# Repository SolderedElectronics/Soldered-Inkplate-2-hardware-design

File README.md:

# Inkplate 2 Hardware design

## About the product

|  |
| :----------------------------------------------------------: |
|      [Buy Inkplate 2](https://www.solde.red/333166)      |

The Inkplate 2 is an Arduino-compatible board that features a 2.13" three-color e-paper display. It is a plug-and-play device, programmable via USB port, and controlled by an ESP32 microcontroller. Moreover, it connects to the internet via WiFi or Bluetooth. Since it uses only 8uA in low-power mode, it can last for months on a single Li-ion battery charge. It's simple enough to be used by beginners, but it also offers plenty of features and a user-friendly platform for advanced users. Inkplate 2 has it all, packed on a small-factor board.

If you're like us, when you first saw an e-book reader, you thought "If only I could use a screen like this in my project". Thanks to the exceptional sharpness and contrast, the ability to display in sunlight and truly unprecedented efficiency in terms of energy (it consumes energy only when changing the content on the screen), electronic paper is the ideal choice for many applications. Inkplate 2, continuing the tradition of the now well-known Inkplate series, offers a variation of e-paper accessible to hobbyists and everyone else in a way that we have created a plug-and-play hardware that is really easy to use, and is compatible with Arduino and micropython.

## Repository contents

All Soldered Electronics hardware designed in KiCAD, and repositories are organized in the following way:

- CAD folder - contains KiCAD files (Schematics, Board, Panel Board), sorted by version. Change log lists all changes between versions.
- OUTPUTS - contains useful files, such as Bill of Materials (BOM), PDF of schematics, 3D .step file of the board and gerber files, sorted by version. 
- OUTPUTS -> Compliance - Certificates and useful legal stuff. 

## Want to contribute?

Please feel free to submit a pull request if you have any contributions. We encourage you to submit an issue or pull request if you find a bug. 

## About Soldered

At Soldered, we design and manufacture a wide selection of electronic products to help you turn your ideas into acts and bring you one step closer to your final project. Our products are intented for makers and crafted in-house by our experienced team in Osijek, Croatia. We believe that sharing is a crucial element for improvement and innovation, and we work hard to stay connected with all our makers regardless of their skill or experience level. Therefore, all our products are open-source. Finally, we always have your back. If you face any problem concerning either your shopping experience or your electronics project, our team will help you deal with it, offering efficient customer service and cost-free technical support anytime. Some of those might be useful for you:

- [Web Store](https://www.soldered.com/shop)
- [Tutorials & Projects](https://soldered.com/learn)
- [Community & Technical support](https://soldered.com/community)

## License info

All Soldered open-source hardware (OSH) is under The TAPR Open Hardware License. Read more in the LICENSE file. 

No warranty - all designs in this repository are distributed in the hope that they will be useful, but without any warranty. They are provided "AS IS", therefore without warranty of any kind, either expressed or implied. The entire quality and performance of what you do with the contents of this repository are your responsibility. In no event, Soldered Electronics will be liable for your damages, losses, including any general, special, incidental or consequential damage arising out of the use or inability to use the contents of this repository. 

## Have fun! 
And thank you from your fellow makers at Soldered Electronics.

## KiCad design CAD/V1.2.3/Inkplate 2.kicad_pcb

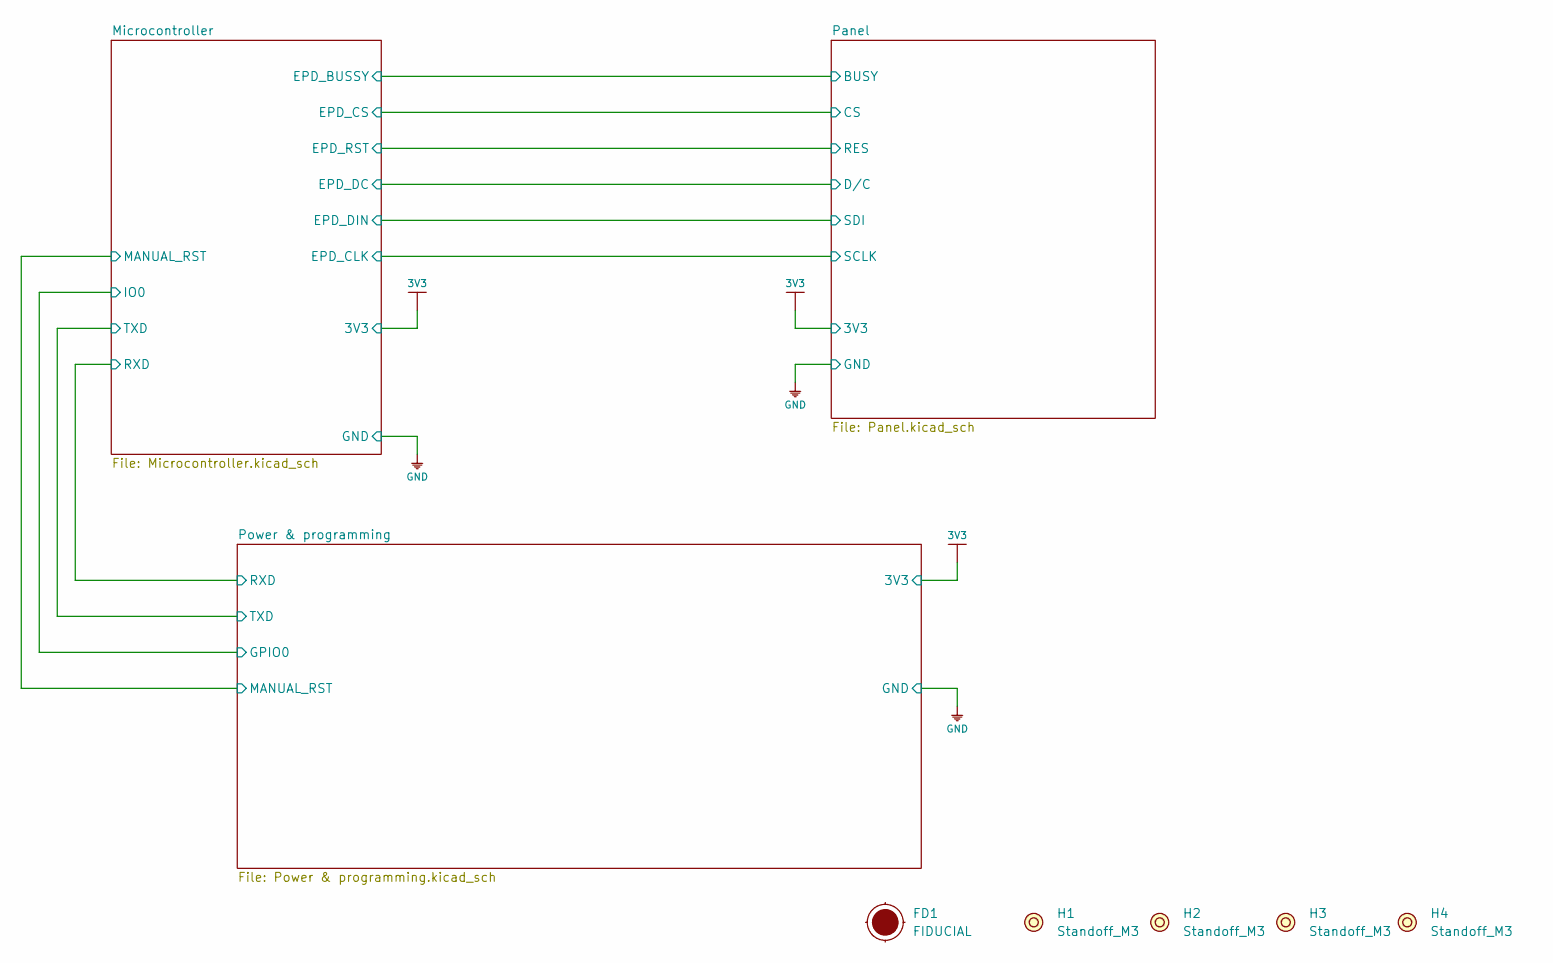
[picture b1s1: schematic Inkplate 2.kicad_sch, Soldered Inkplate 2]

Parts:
FD1: FIDUCIAL; FIDUCIAL_23
H1, H2, H3, H4: Standoff_M3

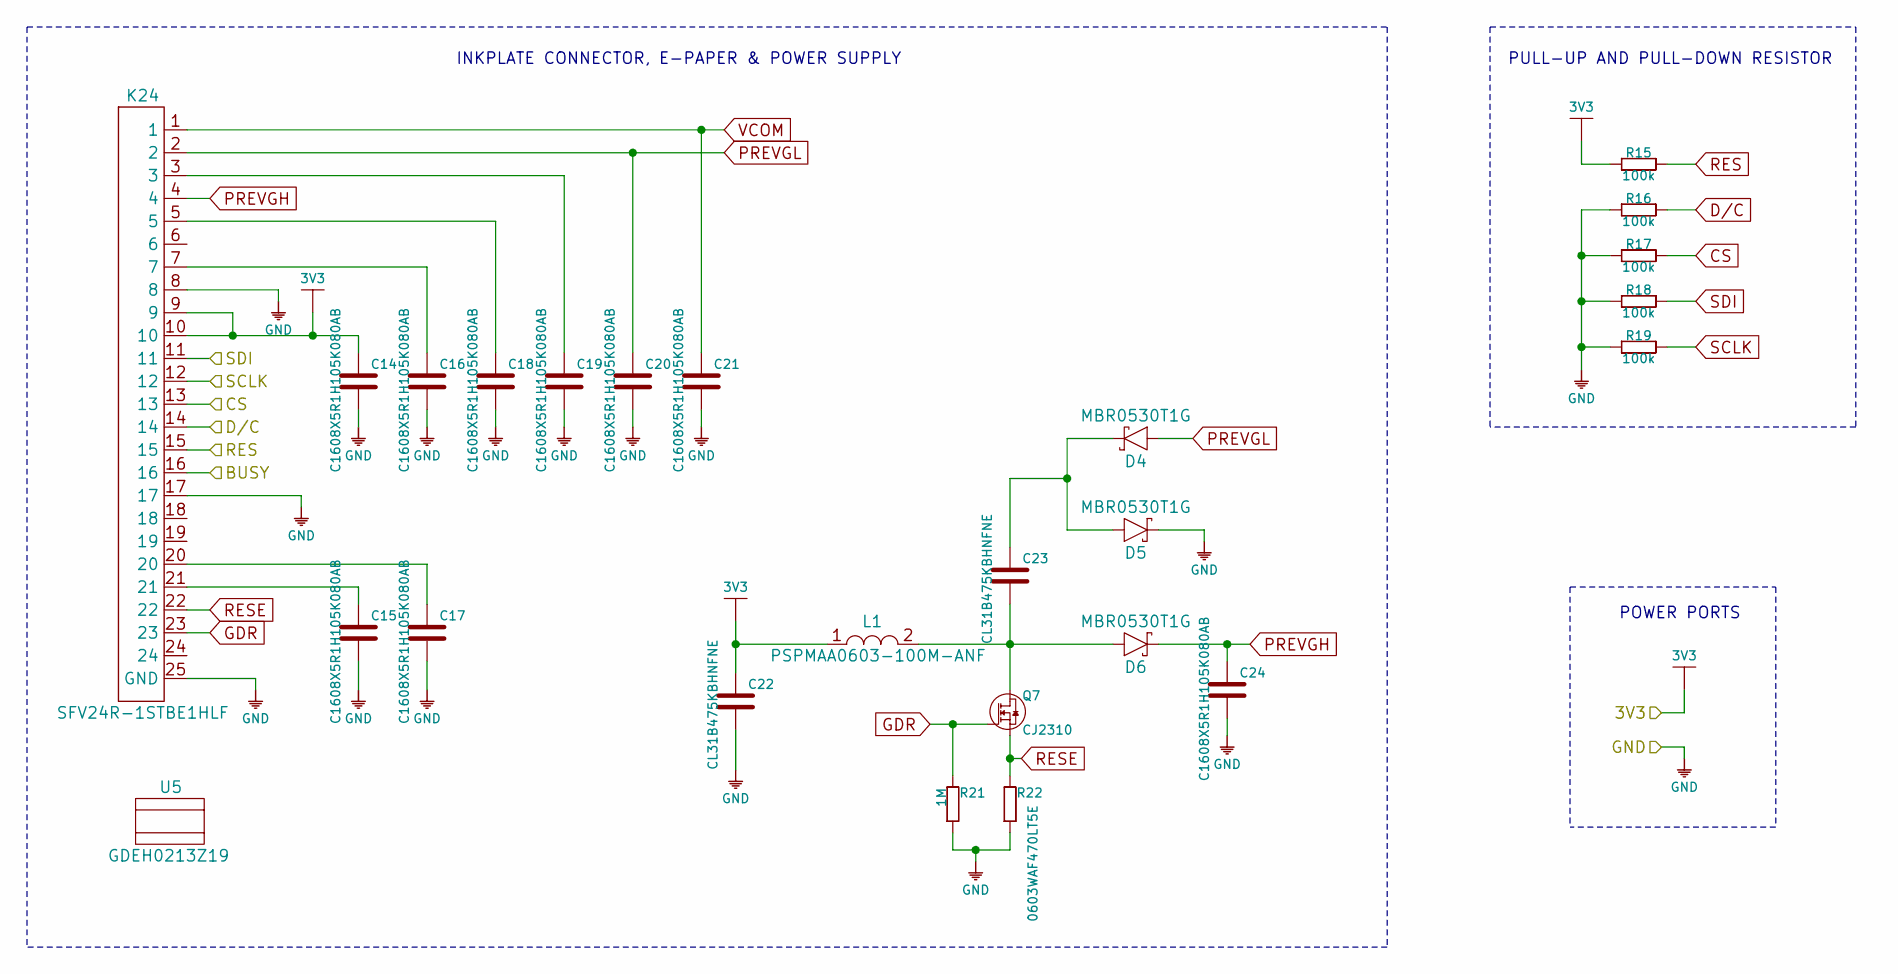
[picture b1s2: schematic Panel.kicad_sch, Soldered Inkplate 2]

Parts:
C14, C15, C16, C17, C18, C19, C20, C21, C24: C1608X5R1H105K080AB; 0603C
C22, C23: CL31B475KBHNFNE; 1206C
D4, D5, D6: MBR0530T1G; SOD-123
K24: SFV24R-1STBE1HLF; SFV24R-2STBE1HLF
L1: PSPMAA0603-100M-ANF; Inductor_SMD_7x6.6
Q7: CJ2310; SOT-23-3
R15, R16, R17, R18, R19: 100k; 0603R
R21: 1M; 0603R
R22: 0603WAF470LT5E; 0603R
U5: GDEH0213Z19

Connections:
3V3: C14.2, C22.2, K24.9, K24.10, L1.1, R15.1; also elsewhere on the board
/Microcontroller/EPD_BUSSY: K24.16; also elsewhere on the board
CS: K24.13, R17.2; also elsewhere on the board
D/C: K24.14, R16.2; also elsewhere on the board
GDR: K24.23, Q7.1 (G), R21.2
GND: C14.1, C15.1, C16.1, C17.1, C18.1, C19.1, C20.1, C21.1, C22.1, C24.1, D5.1 (C), K24.8, K24.17, K24.25 (GND), R16.1, R17.1, R18.1, R19.1, R21.1, R22.1; also elsewhere on the board
unnamed: C15.2, K24.21
unnamed: C16.2, K24.7
unnamed: C17.2, K24.20
unnamed: C18.2, K24.5
unnamed: C19.2, K24.3
unnamed: C23.1, D6.2 (A), L1.2, Q7.3 (D)
unnamed: C23.2, D4.1 (C), D5.2 (A)
PREVGH: C24.2, D6.1 (C), K24.4
PREVGL: C20.2, D4.2 (A), K24.2
RES: K24.15, R15.2; also elsewhere on the board
RESE: K24.22, Q7.2 (S), R22.2
SCLK: K24.12, R19.2; also elsewhere on the board
SDI: K24.11, R18.2; also elsewhere on the board
VCOM: C21.2, K24.1

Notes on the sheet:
INKPLATE CONNECTOR, E-PAPER & POWER SUPPLY
POWER PORTS
PULL-UP AND PULL-DOWN RESISTOR

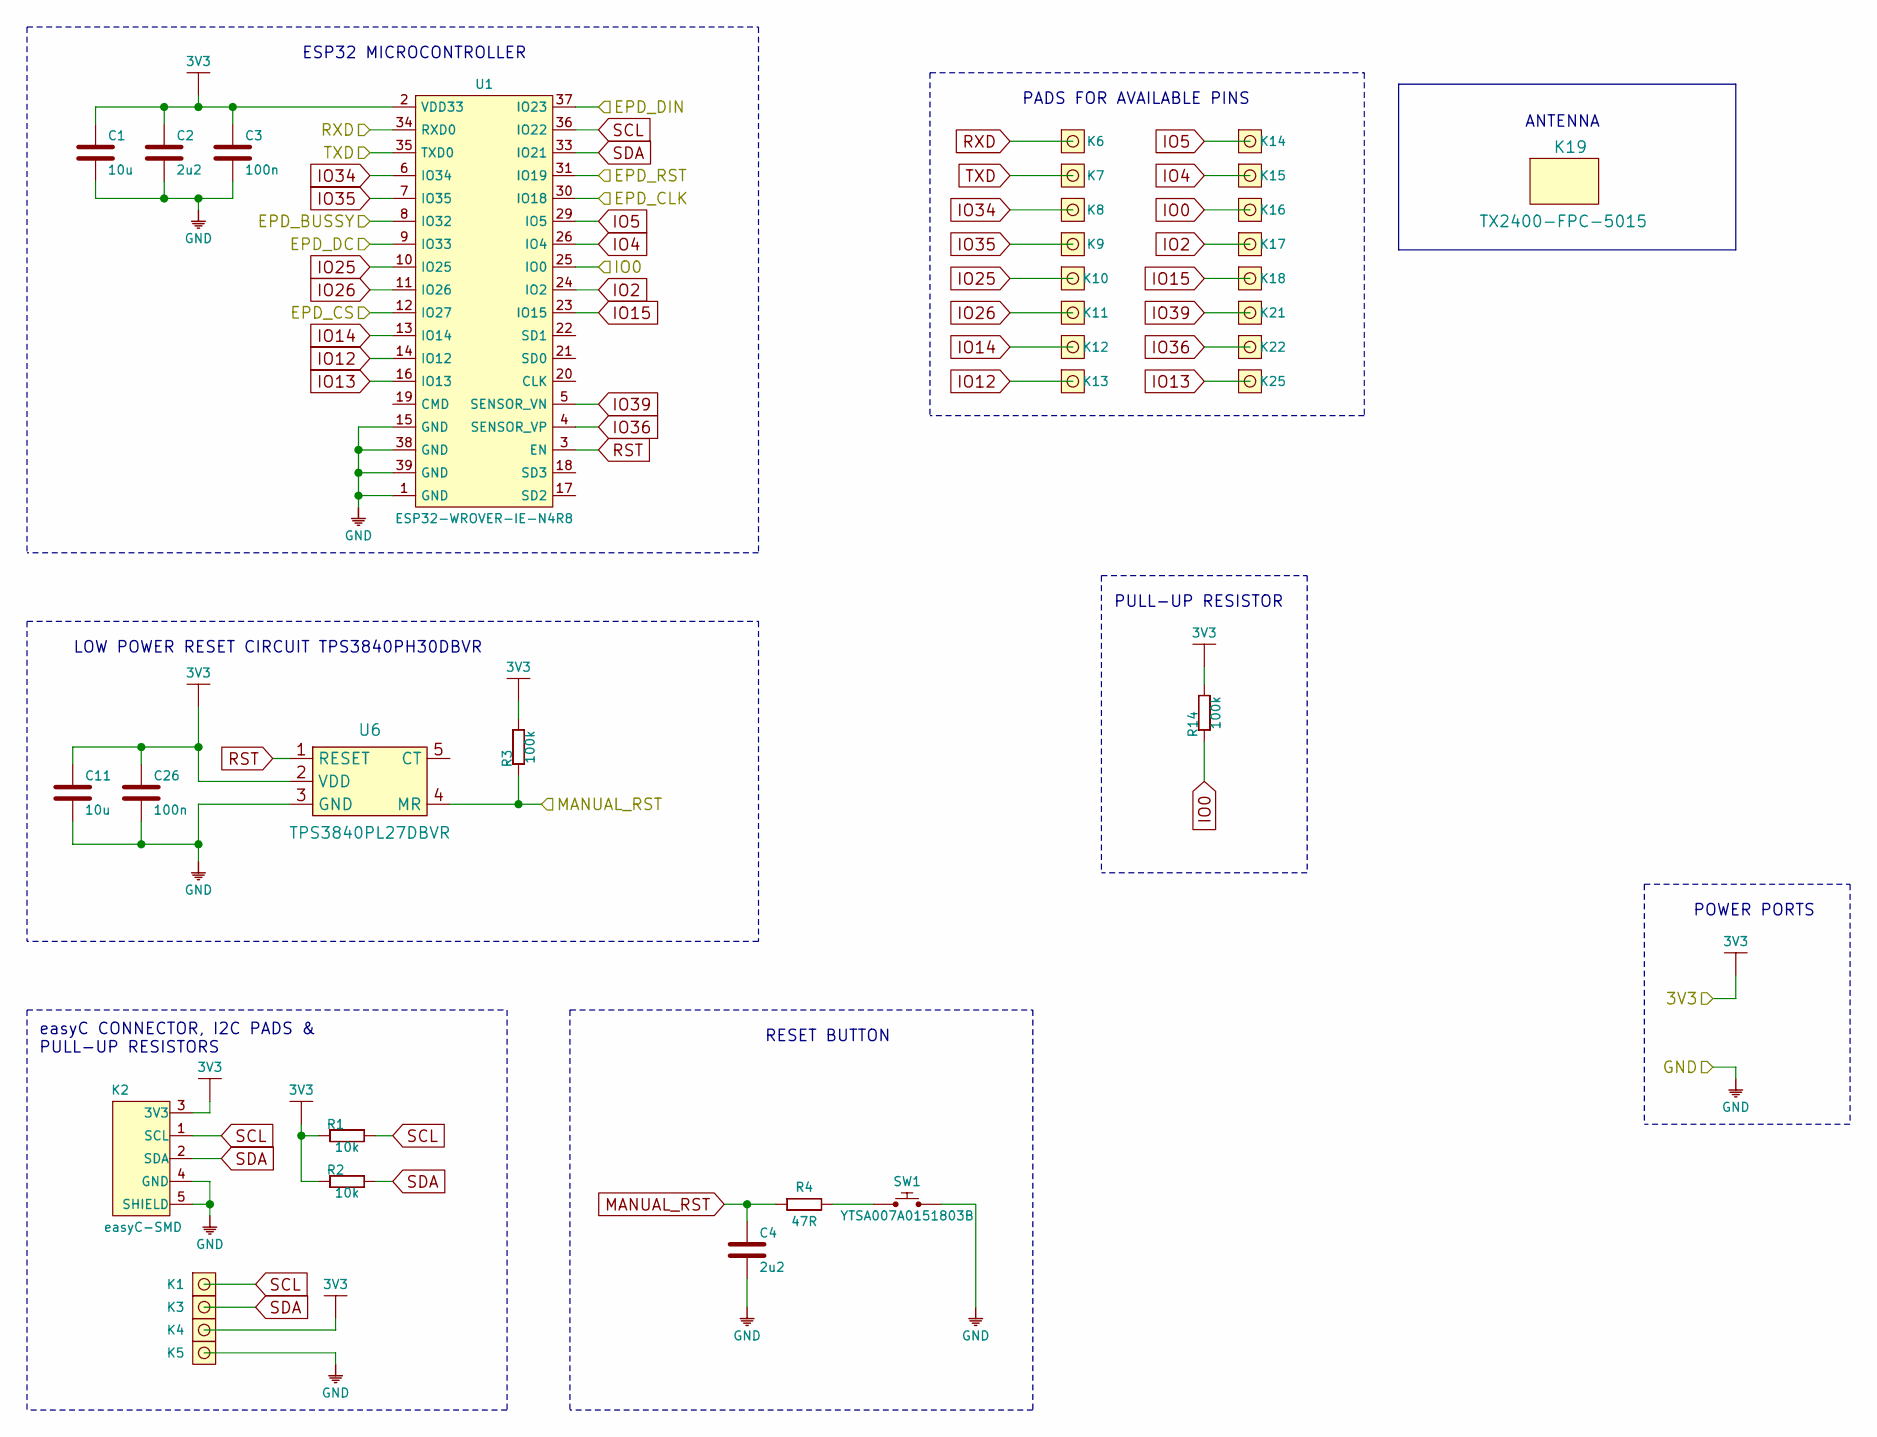
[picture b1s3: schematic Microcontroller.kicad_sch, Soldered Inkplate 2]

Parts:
C1, C11: 10u; 1206C
C2, C4: 2u2; 0603C
C3, C26: 100n; 0603C
K1, K3, K4, K5, K6, K7, K8, K9, K10, K11, K12, K13, K14, K15, K16, K17, K18, K21, K22, K25: HEADER_MALE_1X1_Inkplate
K2: easyC-SMD; easyC-connector
K19: TX2400-FPC-5015
R1, R2: 10k; 0603R
R3, R14: 100k; 0603R
R4: 47R; 0603R
SW1: YTSA007A0151803B
U1: ESP32-WROVER-IE-N4R8; ESP32-WROVER
U6: TPS3840PL27DBVR; SOT-23-5

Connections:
3V3: C1.2, C2.2, C3.2, C11.2, C26.2, K2.3 (3V3), K4.1, R1.1, R2.1, R3.2, R14.2, U1.2 (VDD33), U6.2 (VDD); also elsewhere on the board
/Microcontroller/EPD_BUSSY: U1.8 (IO32); also elsewhere on the board
CS: U1.12 (IO27); also elsewhere on the board
D/C: U1.9 (IO33); also elsewhere on the board
GND: C1.1, C2.1, C3.1, C4.1, C11.1, C26.1, K2.4 (GND), K2.5 (SHIELD), K5.1, SW1.2, U1.1 (GND), U1.15 (GND), U1.38 (GND), U1.39 (GND), U6.3 (GND); also elsewhere on the board
IO0: K16.1, R14.1, U1.25 (IO0); also elsewhere on the board
IO2: K17.1, U1.24 (IO2)
IO4: K15.1, U1.26 (IO4)
IO5: K14.1, U1.29 (IO5)
IO12: K13.1, U1.14 (IO12)
IO13: K25.1, U1.16 (IO13)
IO14: K12.1, U1.13 (IO14)
IO15: K18.1, U1.23 (IO15)
IO25: K10.1, U1.10 (IO25)
IO26: K11.1, U1.11 (IO26)
IO34: K8.1, U1.6 (IO34)
IO35: K9.1, U1.7 (IO35)
IO36: K22.1, U1.4 (SENSOR_VP)
IO39: K21.1, U1.5 (SENSOR_VN)
MANUAL_RST: C4.2, R3.1, R4.1, U6.4 (MR); also elsewhere on the board
unnamed: R4.2, SW1.1
RES: U1.31 (IO19); also elsewhere on the board
RST: U1.3 (EN), U6.1 (RESET)
RXD: K6.1, U1.34 (RXD0); also elsewhere on the board
SCL: K1.1, K2.1 (SCL), R1.2, U1.36 (IO22)
SCLK: U1.30 (IO18); also elsewhere on the board
SDA: K2.2 (SDA), K3.1, R2.2, U1.33 (IO21)
SDI: U1.37 (IO23); also elsewhere on the board
TXD: K7.1, U1.35 (TXD0); also elsewhere on the board

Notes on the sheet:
RESET BUTTON
POWER PORTS
LOW POWER RESET CIRCUIT TPS3840PH30DBVR
PULL-UP RESISTOR
ANTENNA
easyC CONNECTOR, I2C PADS & PULL-UP RESISTORS
PADS FOR AVAILABLE PINS
ESP32 MICROCONTROLLER

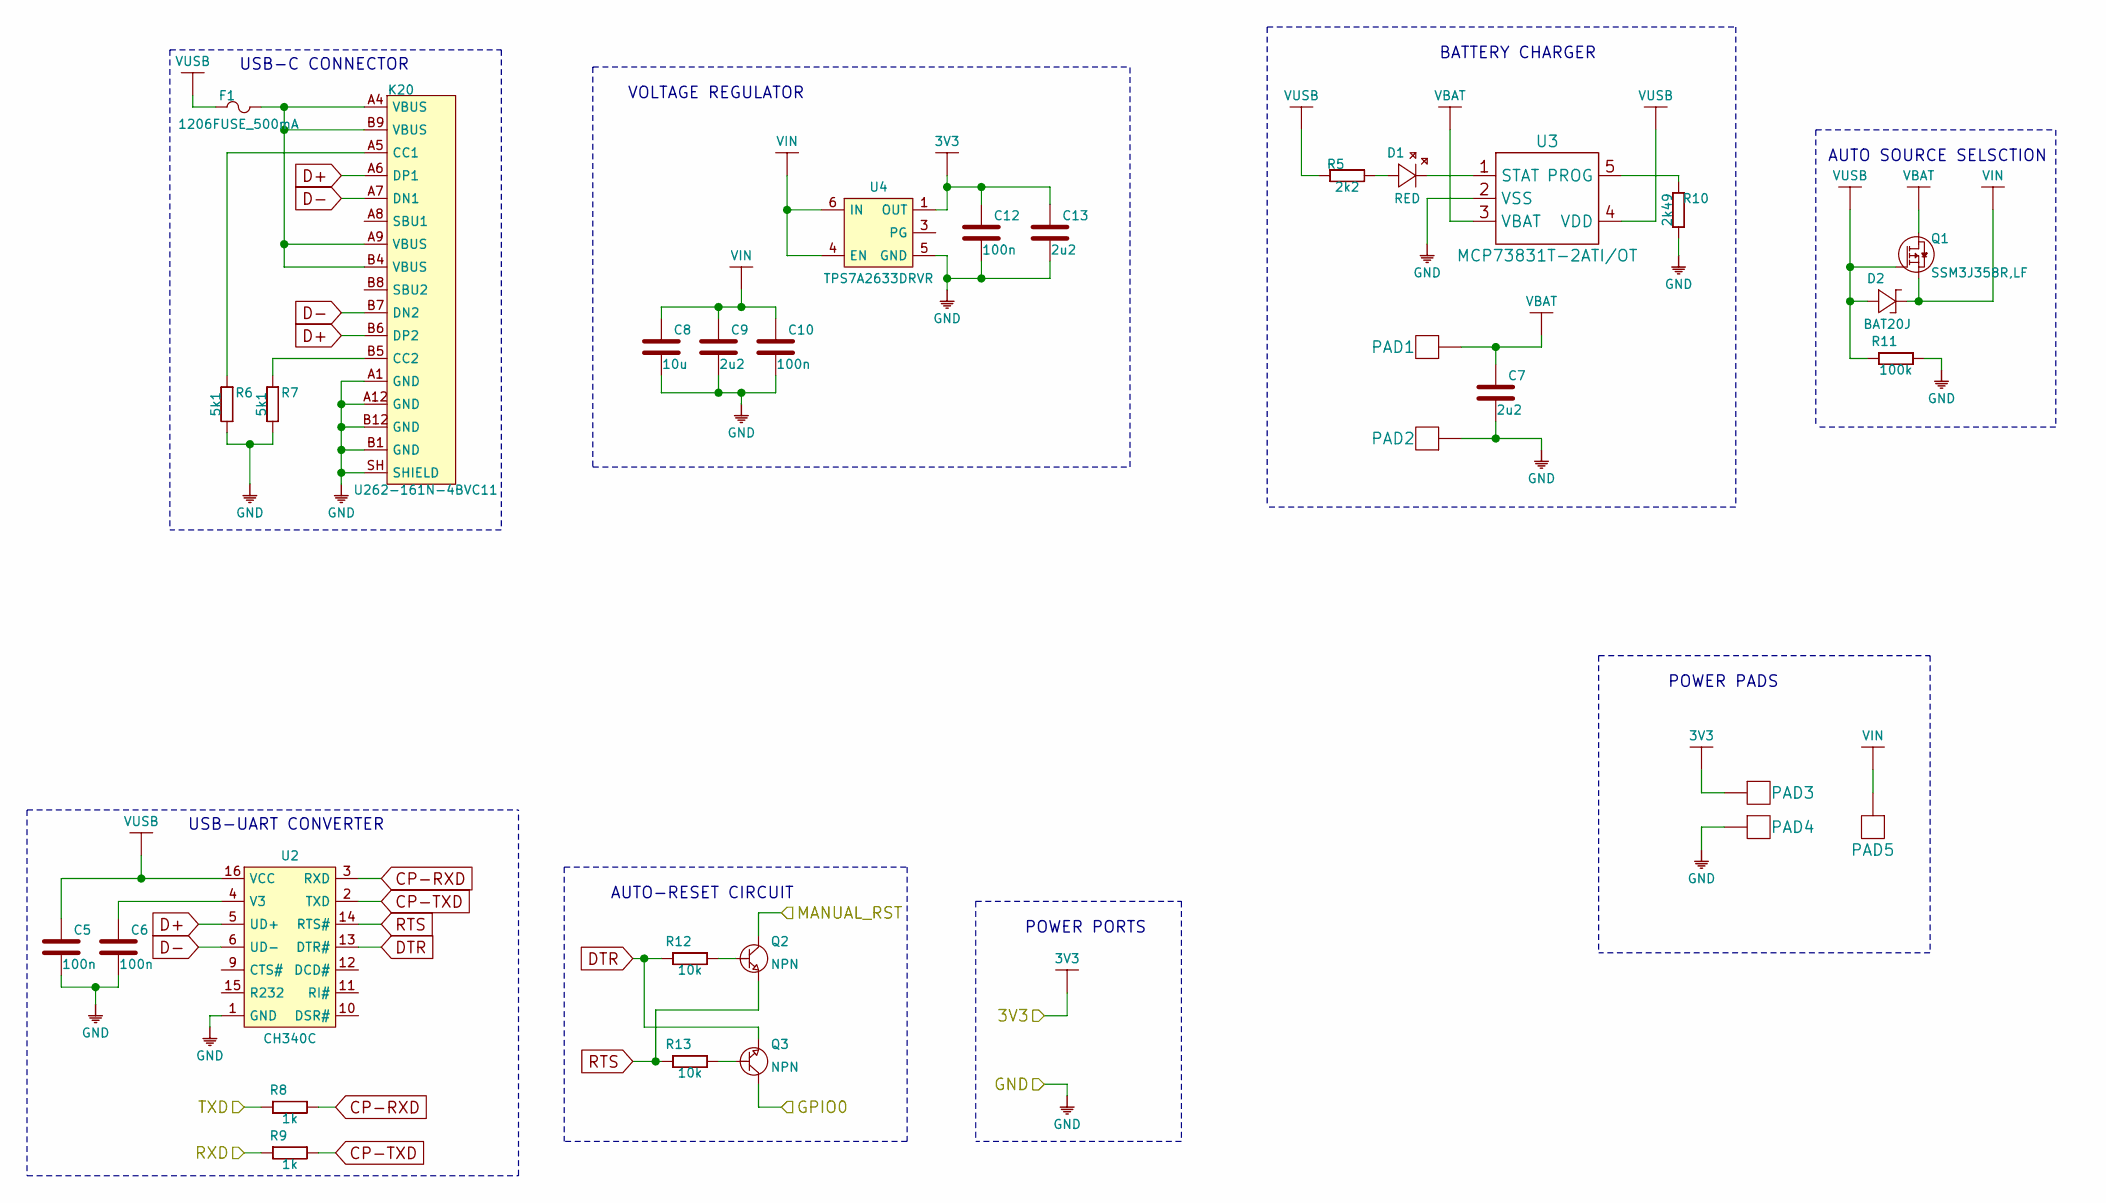
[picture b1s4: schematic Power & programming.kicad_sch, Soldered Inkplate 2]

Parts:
C5, C6, C10, C12: 100n; 0603C
C7, C9, C13: 2u2; 0603C
C8: 10u; 1206C
D1: RED; 0402LED
D2: BAT20J; SOD-323
F1: 1206FUSE_500mA; 1206FUSE
K20: U262-161N-4BVC11
PAD1, PAD2, PAD3, PAD4, PAD5: PAD_2x1.5
Q1: SSM3J358R,LF; SOT-23-3
Q2, Q3: NPN; SOT-23-3
R5: 2k2; 0402R
R6, R7: 5k1; 0603R
R8, R9: 1k; 0603R
R10: 2k49; 0603R
R11: 100k; 0603R
R12, R13: 10k; 0603R
U2: CH340C; SOP-16
U3: MCP73831T-2ATI/OT; SOT-23-5
U4: TPS7A2633DRVR

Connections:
3V3: C12.2, C13.2, PAD3.1, U4.1 (OUT); also elsewhere on the board
CP-RXD: R8.2, U2.3 (RXD)
CP-TXD: R9.2, U2.2 (TXD)
D+: K20.A6 (DP1), K20.B6 (DP2), U2.5 (UD+)
D-: K20.A7 (DN1), K20.B7 (DN2), U2.6 (UD-)
DTR: Q3.2 (E), R12.1, U2.13 (DTR#)
GND: C5.1, C6.1, C7.1, C8.1, C9.1, C10.1, C12.1, C13.1, K20.A1 (GND), K20.A12 (GND), K20.B1 (GND), K20.B12 (GND), K20.SH (SHIELD), PAD2.1, PAD4.1, R6.2, R7.2, R10.2, R11.2, U2.1 (GND), U3.2 (VSS), U4.5 (GND); also elsewhere on the board
IO0: Q3.3 (C); also elsewhere on the board
MANUAL_RST: Q2.3 (C); also elsewhere on the board
unnamed: C6.2, U2.4 (V3)
unnamed: D1.1 (A), R5.2
unnamed: D1.2 (K), U3.1 (STAT)
unnamed: F1.2, K20.A4 (VBUS), K20.A9 (VBUS), K20.B4 (VBUS), K20.B9 (VBUS)
unnamed: K20.A5 (CC1), R6.1
unnamed: K20.B5 (CC2), R7.1
unnamed: Q2.1 (B), R12.2
unnamed: Q3.1 (B), R13.2
unnamed: R10.1, U3.5 (PROG)
RTS: Q2.2 (E), R13.1, U2.14 (RTS#)
RXD: R9.1; also elsewhere on the board
TXD: R8.1; also elsewhere on the board
VBAT: C7.2, PAD1.1, Q1.3 (D), U3.3 (VBAT)
VIN: C8.2, C9.2, C10.2, D2.2 (K), PAD5.1, Q1.2 (S), U4.4 (EN), U4.6 (IN)
VUSB: C5.2, D2.1 (A), F1.1, Q1.1 (G), R5.1, R11.1, U2.16 (VCC), U3.4 (VDD)

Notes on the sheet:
POWER PORTS
POWER PADS
BATTERY CHARGER
VOLTAGE REGULATOR
AUTO-RESET CIRCUIT
AUTO SOURCE SELSCTION
USB-C CONNECTOR
USB-UART CONVERTER

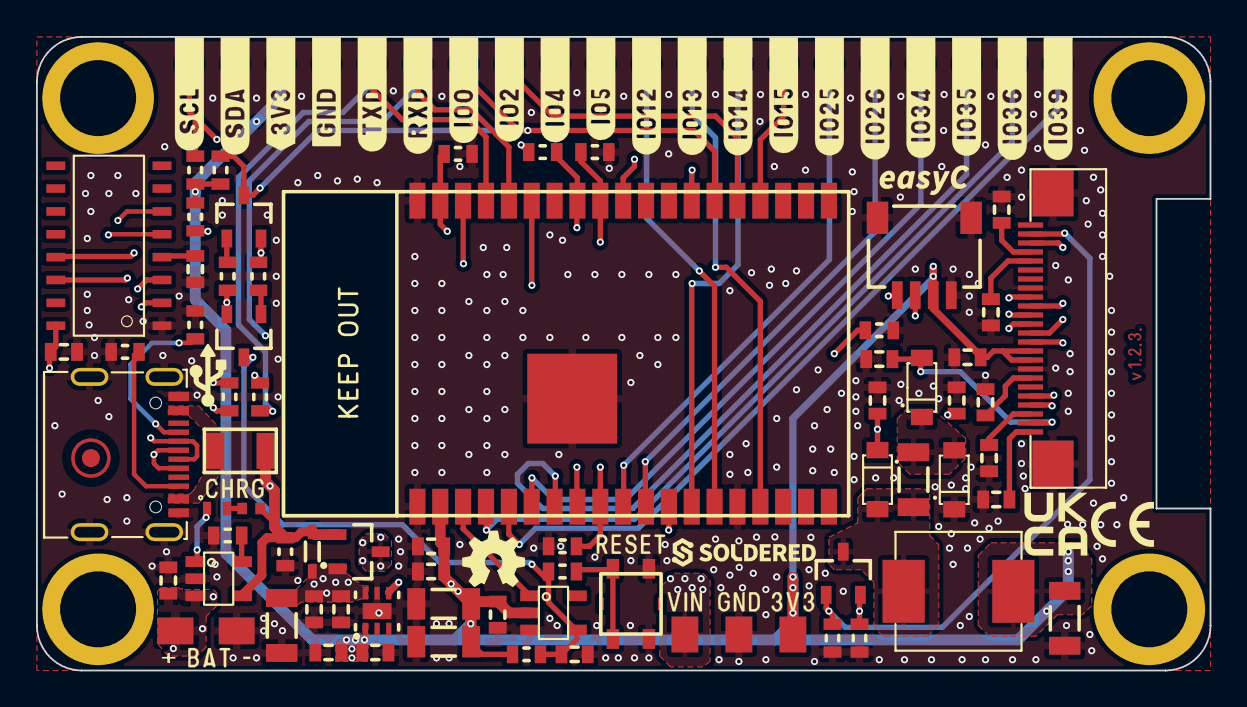
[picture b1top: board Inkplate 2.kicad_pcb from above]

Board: 4 copper layers, 65.2 x 35.2 mm, 98 parts (1 on the bottom side), 59 nets.

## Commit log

2023-06-09 Updating open source files.
